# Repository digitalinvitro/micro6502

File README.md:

# micro6502

6502 cpu based micro module (for mcu applications)

Hardware

- CPU mos6502 - 1MHz
- 16 IO port in zero-page low address (0x0000...0x000F)
- 64K SRAM
- UART RX/TX
- load 256-byte MONITOR to SRAM from UART (terminal) on power on
- 16-bit address bus, 8-bit data bus, control bus and 16 IO pin to pinheaders connected
- option spi/i2c/SN74HC595/dendy joystik(HEF4021B) interfaces HDL programmed in CPLD

Программное обеспечение:
* АССЕМБЛЕР - naken asm http://www.mikekohn.net/micro/naken_asm.php
* МОНИТОР   - программное обеспечение для начальной загрузки модуля по включению питания. Загружается с адреса 0xFF00, после загрузки 256 байт кода, на процессор подается питание с последюущим сбросом по лининии reset. 
* ОТЛАДЧИК  - программное обеспечение для отладки загружаемого кода, интерфейс строчный. Загружается с адреса 0x1000.

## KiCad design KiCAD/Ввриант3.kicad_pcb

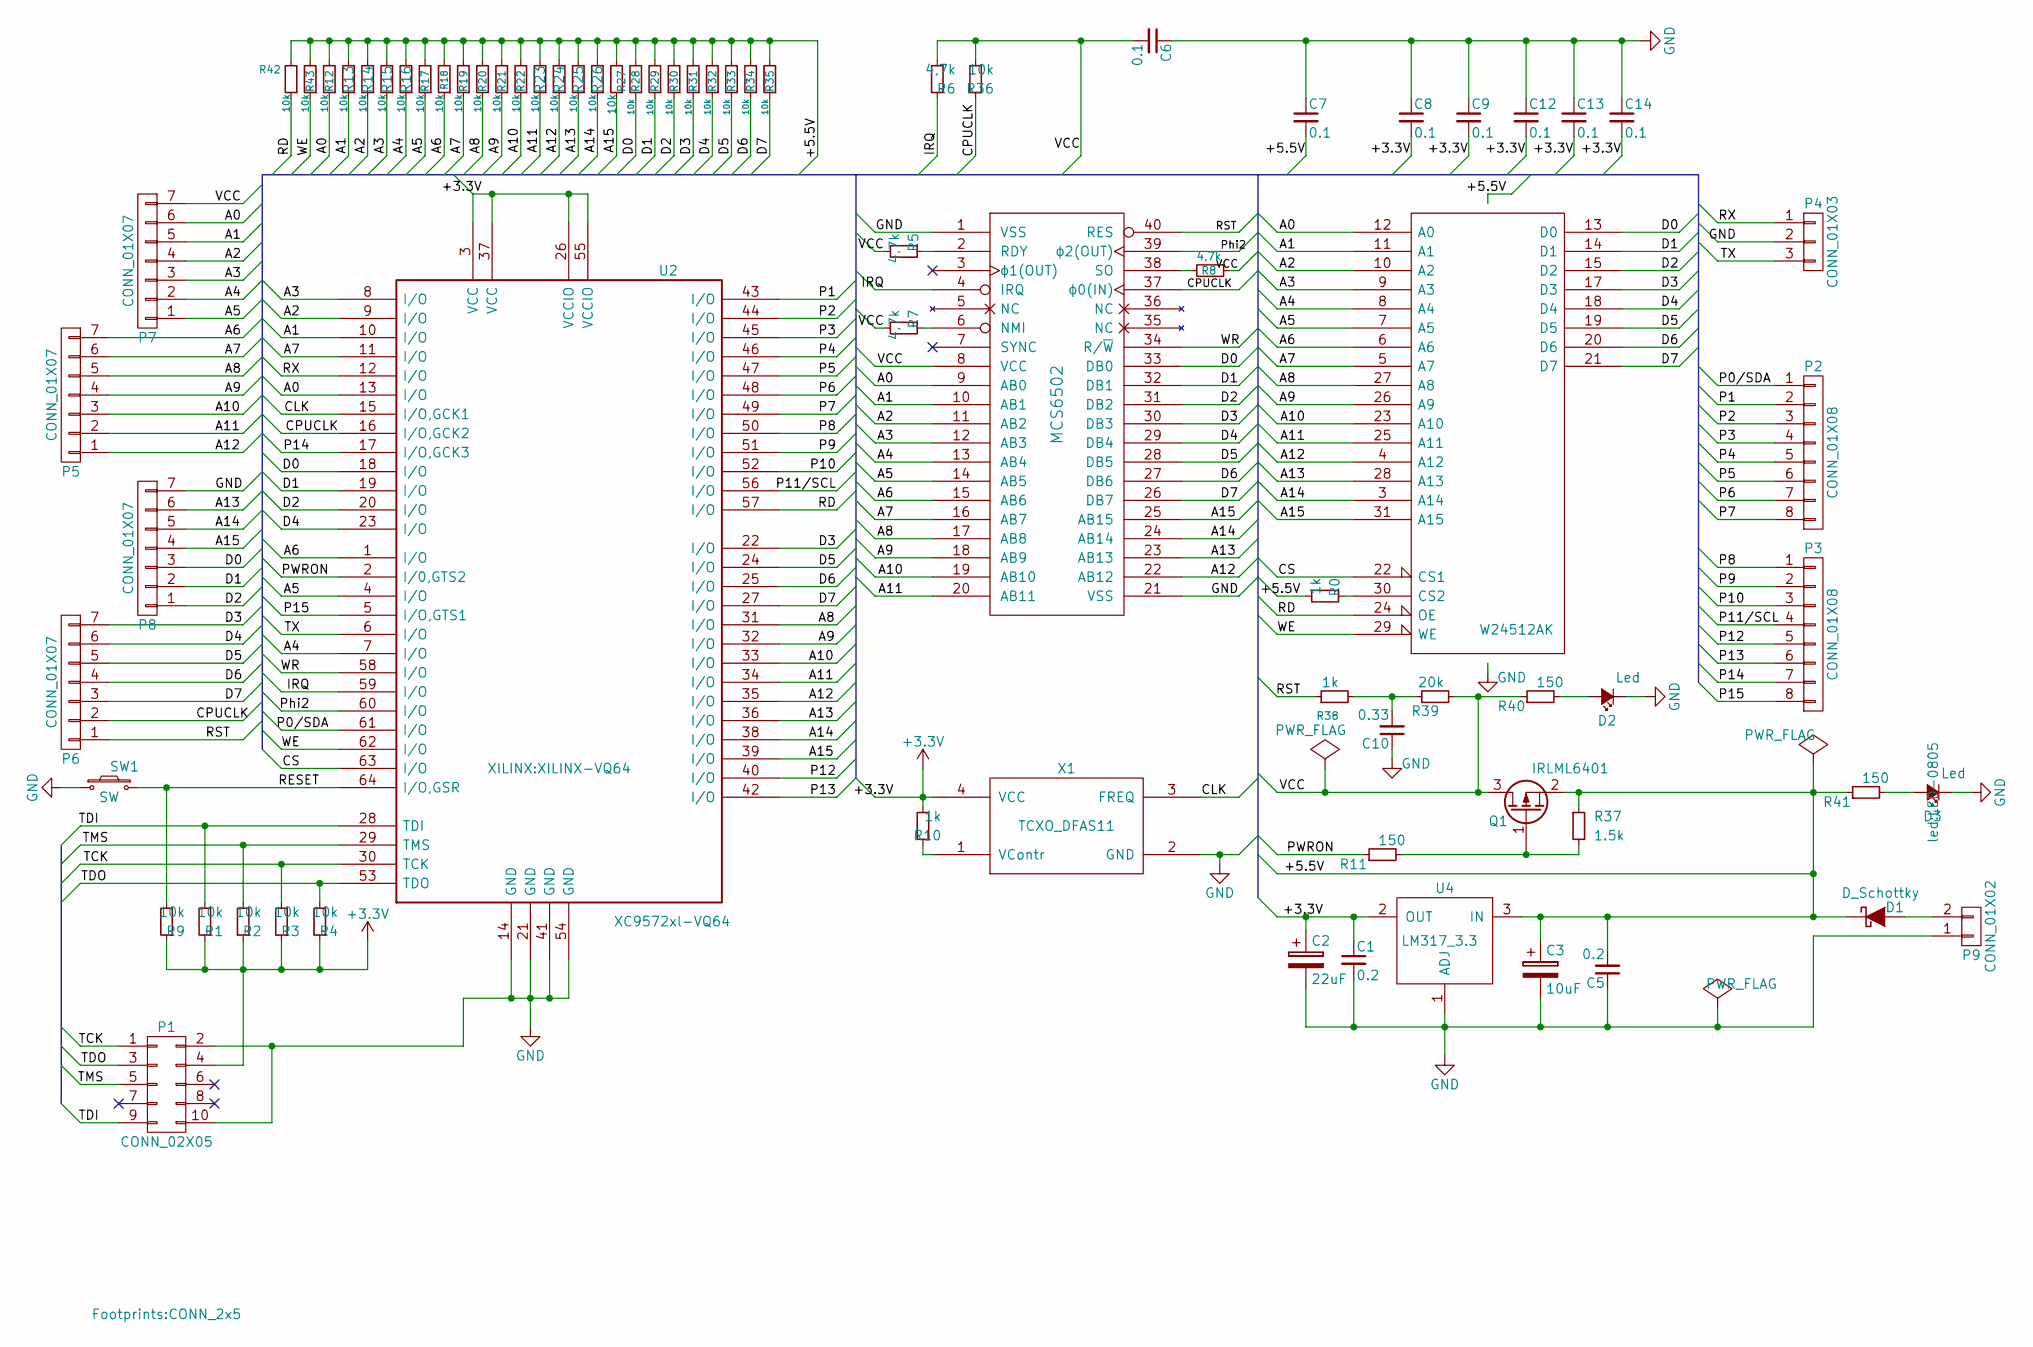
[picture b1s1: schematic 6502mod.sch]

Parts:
C1: 0.2; m-pad-2.1-0603
C2: 22uF; C1V5
C3: 10uF; C1V5
C5: 0.2; m-pad-2.1-0603P
C6, C7, C8, C9, C12, C13, C14: 0.1; m-pad-2.1-0603P
C10: 0.33; m-pad-2.1-0603
D1: D_Schottky; m-pad-2.1-1206P
D2, D3: Led; LED-0805
P1: CONN_02X05; CONN_2x5
P2, P3: CONN_01X08; CONN_1x8
P4: CONN_01X03; CONN_1x3
P5, P6, P7, P8: CONN_01X07; CONN_1x7
P9: CONN_01X02; connect-CLAMP-02
Q1: IRLML6401; transistor-SOT23
R0, R10, R38: 1k; m-pad-2.1-0603
R1, R2, R3, R4, R9, R12, R13, R14, R15, R16, R17, R18, R19, R20, R21, R22, R23, R24, R25, R26, R27, R28, R29, R30, R31, R32, R33, R34, R35, R36, R42, R43: 10k; m-pad-2.1-0603
R5, R6, R7, R8: 4,7k; m-pad-2.1-0603
R11, R40, R41: 150; m-pad-2.1-0603
R37: 1.5k; m-pad-2.1-0603
R39: 20k; m-pad-2.1-0603
SW1: SW; SW_SPST_EVQP0
U1: MCS6502; DIP-40_W15.24mm
U2: XC9572xl-VQ64; XILINX-VQ64
U3: W24512AK; DIP-32_W7.62mm
U4: LM317_3.3; m-pad-2.1-SOT223
X1: TCXO_DFAS11; m-pad-2.1-ASVK

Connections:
+3V3: C1.1, C2.1, C8.2, C9.2, C12.2, C13.2, C14.2, P1.4, R1.1, R2.1, R3.1, R4.1, R9.1, R10.2, U2.3 (VCC), U2.26 (VCCIO), U2.37 (VCC), U2.55 (VCCIO), U4.2 (OUT), X1.4 (VCC)
/+5.5V: C3.1, C5.2, C7.2, D1.1 (K), Q1.2 (S), R0.2, R12.2, R13.2, R14.2, R15.2, R16.2, R17.2, R18.2, R19.2, R20.2, R21.2, R22.2, R23.2, R24.2, R25.2, R26.2, R27.2, R28.2, R29.2, R30.2, R31.2, R32.2, R33.2, R34.2, R35.2, R37.1, R41.1, R42.2, R43.2, U3.32 (VCC), U4.3 (IN)
/A0: P7.6, R12.1, U1.9 (AB0), U2.13 (I/O), U3.12 (A0)
/A1: P7.5, R13.1, U1.10 (AB1), U2.10 (I/O), U3.11 (A1)
/A2: P7.4, R14.1, U1.11 (AB2), U2.9 (I/O), U3.10 (A2)
/A3: P7.3, R15.1, U1.12 (AB3), U2.8 (I/O), U3.9 (A3)
/A4: P7.2, R16.1, U1.13 (AB4), U2.7 (I/O), U3.8 (A4)
/A5: P7.1, R17.1, U1.14 (AB5), U2.4 (I/O), U3.7 (A5)
/A6: P5.7, R18.1, U1.15 (AB6), U2.1 (I/O), U3.6 (A6)
/A7: P5.6, R19.1, U1.16 (AB7), U2.11 (I/O), U3.5 (A7)
/A8: P5.5, R20.1, U1.17 (AB8), U2.31 (I/O), U3.27 (A8)
/A9: P5.4, R21.1, U1.18 (AB9), U2.32 (I/O), U3.26 (A9)
/A10: P5.3, R22.1, U1.19 (AB10), U2.33 (I/O), U3.23 (A10)
/A11: P5.2, R23.1, U1.20 (AB11), U2.34 (I/O), U3.25 (A11)
/A12: P5.1, R24.1, U1.22 (AB12), U2.35 (I/O), U3.4 (A12)
/A13: P8.6, R25.1, U1.23 (AB13), U2.36 (I/O), U3.28 (A13)
/A14: P8.5, R26.1, U1.24 (AB14), U2.38 (I/O), U3.3 (A14)
/A15: P8.4, R27.1, U1.25 (AB15), U2.39 (I/O), U3.31 (A15)
/CLK: U2.15 (I/O,GCK1), X1.3 (FREQ)
/CPUCLK: P6.2, R36.1, U1.37 (ɸ0(IN)), U2.16 (I/O,GCK2)
/CS: U2.63 (I/O), U3.22 (CS1)
/D0: P8.3, R28.1, U1.33 (DB0), U2.18 (I/O), U3.13 (D0)
/D1: P8.2, R29.1, U1.32 (DB1), U2.19 (I/O), U3.14 (D1)
/D2: P8.1, R30.1, U1.31 (DB2), U2.20 (I/O), U3.15 (D2)
/D3: P6.7, R31.1, U1.30 (DB3), U2.22 (I/O), U3.17 (D3)
/D4: P6.6, R32.1, U1.29 (DB4), U2.23 (I/O), U3.18 (D4)
/D5: P6.5, R33.1, U1.28 (DB5), U2.24 (I/O), U3.19 (D5)
/D6: P6.4, R34.1, U1.27 (DB6), U2.25 (I/O), U3.20 (D6)
/D7: P6.3, R35.1, U1.26 (DB7), U2.27 (I/O), U3.21 (D7)
/IRQ: R6.1, U1.4 (IRQ), U2.59 (I/O)
/P0/SDA: P2.1, U2.61 (I/O)
/P1: P2.2, U2.43 (I/O)
/P2: P2.3, U2.44 (I/O)
/P3: P2.4, U2.45 (I/O)
/P4: P2.5, U2.46 (I/O)
/P5: P2.6, U2.47 (I/O)
/P6: P2.7, U2.48 (I/O)
/P7: P2.8, U2.49 (I/O)
/P8: P3.1, U2.50 (I/O)
/P9: P3.2, U2.51 (I/O)
/P10: P3.3, U2.52 (I/O)
/P11/SCL: P3.4, U2.56 (I/O)
/P12: P3.5, U2.40 (I/O)
/P13: P3.6, U2.42 (I/O)
/P14: P3.7, U2.17 (I/O,GCK3)
/P15: P3.8, U2.5 (I/O,GTS1)
/PWRON: R11.1, U2.2 (I/0,GTS2)
/Phi2: U1.39 (ɸ2(OUT)), U2.60 (I/O)
/RD: R42.1, U2.57 (I/O), U3.24 (OE)
/RESET: R9.2, SW1.2, U2.64 (I/O,GSR)
/RST: P6.1, R38.1, U1.40 (RES)
/RX: P4.1, U2.12 (I/O)
/TCK: P1.1, R3.2, U2.30 (TCK)
/TDI: P1.9, R1.2, U2.28 (TDI)
/TDO: P1.3, R4.2, U2.53 (TDO)
/TMS: P1.5, R2.2, U2.29 (TMS)
/TX: P4.3, U2.6 (I/O)
/VCC: C6.2, P7.7, Q1.3 (D), R5.2, R6.2, R7.2, R8.1, R36.2, R39.2, R40.1, U1.8 (VCC)
/WE: R43.1, U2.62 (I/O), U3.29 (WE)
/WR: U1.34 (R/~W), U2.58 (I/O)
GND: C1.2, C2.2, C3.2, C5.1, C6.1, C7.1, C8.1, C9.1, C10.1, C12.1, C13.1, C14.1, D2.1, D3.1, P1.2, P1.10, P4.2, P8.7, P9.1, SW1.1, U1.1 (VSS), U1.21 (VSS), U2.14 (GND), U2.21 (GND), U2.41 (GND), U2.54 (GND), U3.16 (GND), U4.1 (ADJ), X1.2 (GND)
unnamed: C10.2, R38.2, R39.1
unnamed: D1.2 (A), P9.2
unnamed: D2.2, R40.2
unnamed: D3.2, R41.2
unnamed: Q1.1 (G), R11.2, R37.2
unnamed: R0.1, U3.30 (CS2)
unnamed: R5.1, U1.2 (RDY)
unnamed: R7.1, U1.6 (NMI)
unnamed: R8.2, U1.38 (SO)
unnamed: R10.1, X1.1 (VContr)

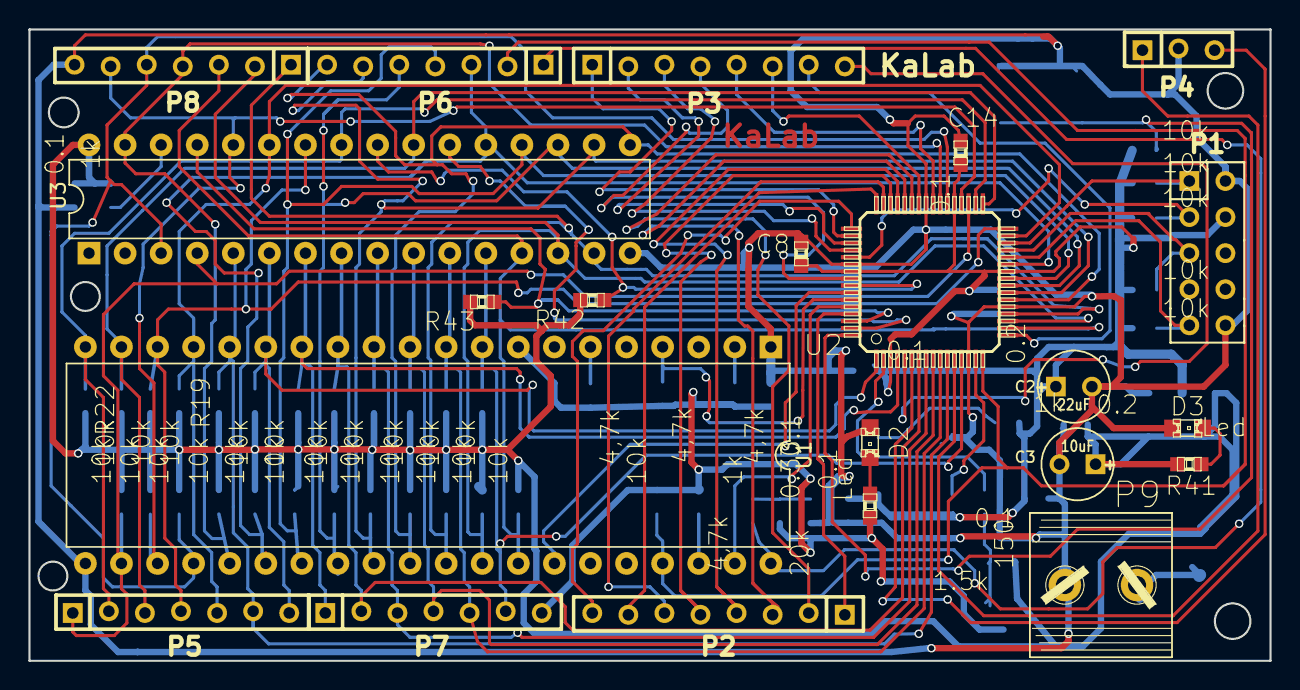
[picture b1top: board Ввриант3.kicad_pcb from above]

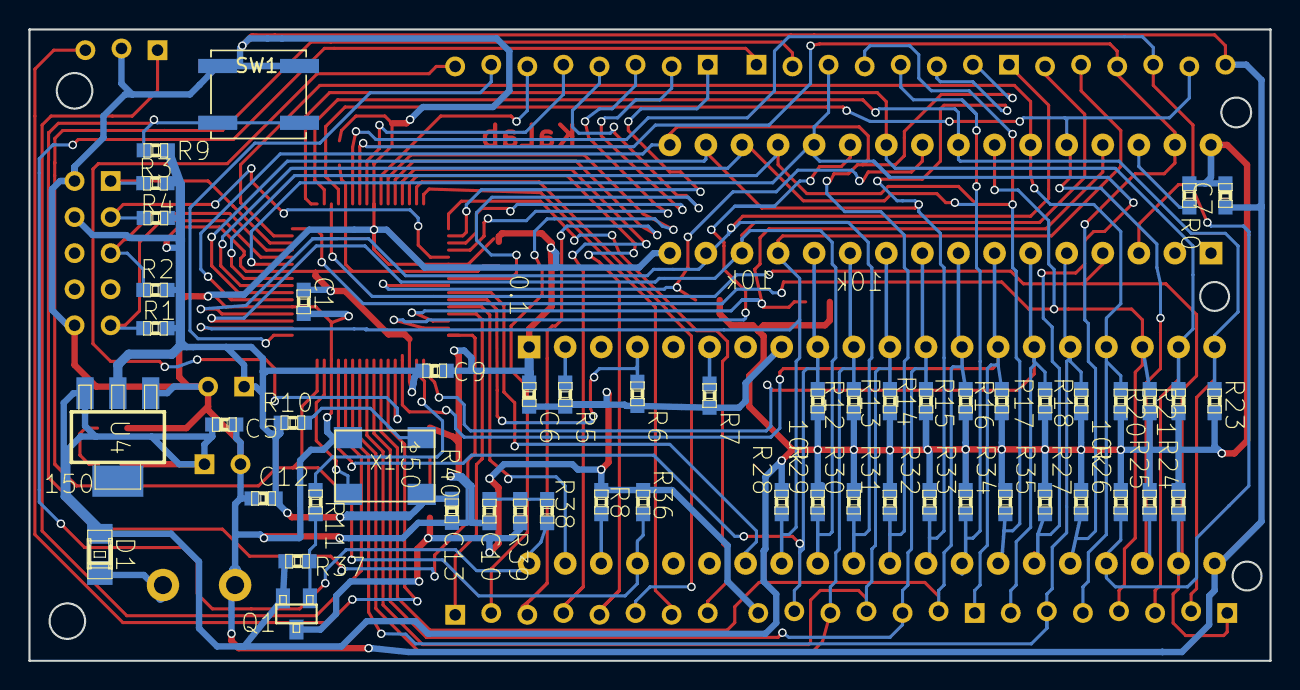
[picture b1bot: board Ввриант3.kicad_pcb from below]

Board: 2 copper layers, 87.4 x 44.5 mm, 75 parts (53 on the bottom side), 71 nets.

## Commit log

2018-05-03 3D view module
2018-05-03 3djpg
2018-05-07 board-description
2018-05-10 booting
2018-10-26 Bin2mos Python tool added
2018-10-28 Initial implementation of u6502 loader
2018-11-07 py3 u6502 loader tool added
2018-11-08 u6502 data loader (py3) fixed
2018-11-08 Fix for linux platform
2018-11-24 Python tools updated
